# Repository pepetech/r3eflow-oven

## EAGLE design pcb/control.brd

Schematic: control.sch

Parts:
B1: PKLCS1212E2400-R1; BUZZ_PIEZO_SMD
C1, C4: 10u; 0603-MINI
C2, C3, C5, C8, C9, C10, C12, C13, C16, C17, C18, C19, C20, C22, C23, C24: 100n; 0603_WAVE
C6: 220u; PANASONIC_D
C7: 470p; 0603_WAVE
C11: CAPACITOR_ELD; PANASONIC_D
C14, C15: MLCC0603; 0603_WAVE
C25: 4u7; 0603_WAVE
C26: 10u; 0603_WAVE
C27: 1u; 0603_WAVE
D1: SK54L; DO214AA
D2, D5, D6: LED0603; CHIPLED_0603
D3: SMAJ36A; DO214AC
D4: SP0503BAHT; SOT143
D7, D8, D9, D10, D11, D12, D13, D14: SK9822; 2020
GND: PTC1812
J1, J3: PCC-SMP
J2: 2X1_2.54
J4: MICROSD; MICRO-SD
J5, J8, J9: 2EDG-2P
J6: 3X1_2.54
J7: 4P-PC-FAN; KF2510-3+1P
J10: USB-C
L1: 6.8uH; _1207
M1: HM-11
Q1, Q2, Q3, Q4: BC817-40; SOT-23-3
R1: 10M; 0603_WAVE
R2: 10k; 0603_WAVE
R3, R11: RESISTOR0603; 0603_WAVE
R4, R23: 100; 0603_WAVE
R5, R20, R21, R22, R28, R35: 100k; 0603_WAVE
R6: 3k01; 0603_WAVE
R7: 953; 0603_WAVE
R8: 300k; 0603_WAVE
R9: 47k; 0603_WAVE
R10, R24, R26, R29, R32: 220; 0603_WAVE
R12, R13, R14, R15: 4k7; 0603_WAVE
R16: 33k; 0603_WAVE
R17, R18, R19, R25, R27: 1k; 0603_WAVE
R30: 22.1k; 0603_WAVE
R31: 47.5k; 0603_WAVE
R33, R34: 5.1k; 0603_WAVE
SW1: PUSH_BUTTON
TC1: TC2050-IDC
U1: MIC4682; SOIC8
U2, U4: MCP9600; TQFN20-5X5
U3: SST26VF064B; WSOIC8
U5, U8, U9: 74LVC1G17; SC70-5
U6: CP2102N; QFN24
U7: ER-TFT035-6BOT; ZIF50-TFT_BACK
U10: EFM32GG11B4XX_Q100; QFP100
Y1: 8MHz; 2-SMD-5X3
Y2: 32.768KHz; CM200S

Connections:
3.3V: C2.P$1, C5.P$1, C8.P$1, C9.P$1, C10.P$1, C12.P$1, C13.P$1, C14.P$1, C15.P$1, C16.P$1, C17.P$1, C18.P$1, C19.P$1, C20.P$1, C22.P$1, C24.P$1, C25.P$1, J4.4, M1.9 (VCC), R3.P$2, R5.P$2, R11.P$2, R12.P$2, R13.P$2, R14.P$2, R15.P$2, R24.P$1, R26.P$1, R28.P$2, R35.P$2, TC1.1, U2.8 (VDD), U3.8 (VCC), U4.8 (VDD), U4.16 (ADDR), U6.5 (VIO), U6.6 (VDD), U6.7 (VREGIN), U7.7 (IM0), U7.8 (IM1), U7.9 (IM2), U7.35 (!RD), U7.40 (VDDI), U7.41 (VDDI), U7.42 (VCI), U10.8 (IOVDD0), U10.17 (IOVDD0), U10.31 (IOVDD0), U10.41 (AVDD), U10.44 (IOVDD0), U10.45 (AVDD), U10.57 (DVDD), U10.73 (VREGO), U10.82 (IOVDD0)
5V: C4.1, C6.+ (AN), C23.P$1, C26.P$1, D7.5 (VDD), D8.5 (VDD), D9.5 (VDD), D10.5 (VDD), D11.5 (VDD), D12.5 (VDD), D13.5 (VDD), D14.5 (VDD), J6.P$2, L1.2, R6.P$2, R21.P$2, R23.P$2, U5.5 (VCC), U7.1 (LEDA), U8.5 (VCC), U9.5 (VCC), U10.72 (VREGI), U10.79 (VBUS)
5V-SENSE: U10.50 (PD4)
12V: C1.1, C11.+ (AN), D3.C, GND.P$1 (1), J7.2, R1.P$2, R8.P$2, R22.P$2, U1.5 (IN)
!5V-ERR: U10.48 (PD2)
!RESET: SW1.1, SW1.2, TC1.10, U10.36 (!RESET)
!TFT_RESET: U7.10 (!RESET), U10.14 (PB5)
!TTFT-IRQ: U7.46 (X-/!IRQ!), U10.12 (PB3)
!TTFT-RST: U7.47 (Y-/!RST!), U10.15 (PB6)
BLE-!RST: M1.11 (!RST!), U10.60 (PE0)
BLE-KEY: M1.16 (PIO0), U10.61 (PE1)
DECOUPLE: C27.P$1, U10.59 (DECOUPLE)
DOOR-SW: C3.P$1, R4.P$2, U10.56 (PC7)
GND: C1.2, C2.P$2, C3.P$2, C4.2, C5.P$2, C6.- (CA), C7.P$2, C8.P$2, C9.P$2, C10.P$2, C11.- (CA), C12.P$2, C13.P$2, C14.P$2, C15.P$2, C16.P$2, C17.P$2, C18.P$2, C19.P$2, C20.P$2, C22.P$2, C23.P$2, C24.P$2, C25.P$2, C26.P$2, C27.P$2, D1.A, D2.C (CA), D3.A, D4.1, D7.2 (GND), D8.2 (GND), D9.2 (GND), D10.2 (GND), D11.2 (GND), D12.2 (GND), D13.2 (GND), D14.2 (GND), J1.3-BAR, J1.4-BAR, J2.2, J3.3-BAR, J3.4-BAR, J4.6, J4.BODY1 (BODY), J4.BODY2 (BODY), J4.BODY3 (BODY), J4.BODY4 (BODY), J5.P$2, J6.P$3, J8.P$1, J9.P$2, J10.A1_B12 (GND), J10.B1_A12 (GND), J10.SHIELD0 (GND), J10.SHIELD1 (GND), J10.SHIELD2 (GND), J10.SHIELD3 (GND), M1.12 (GND), Q1.P$2 (EM2), Q2.P$2 (EM2), Q3.P$2 (EM2), Q4.P$2 (EM2), R2.P$1, R7.P$1, R9.P$1, R16.P$1, R25.P$1, R31.P$1, R33.P$1, R34.P$1, SW1.3, SW1.4, TC1.3, TC1.9, U1.2 (GND), U1.4 (SHDN), U1.6 (GND), U1.7 (GND), U2.1 (GND), U2.3 (GND), U2.5 (GND), U2.6 (GND), U2.7 (GND), U2.9 (GND), U2.10 (GND), U2.13 (GND), U2.16 (ADDR), U2.17 (GND), U2.18 (GND), U2.EXP (EP), U3.4 (GND), U4.1 (GND), U4.3 (GND), U4.5 (GND), U4.6 (GND), U4.7 (GND), U4.9 (GND), U4.10 (GND), U4.13 (GND), U4.17 (GND), U4.18 (GND), U4.EXP (EP), U5.3 (GND), U6.2 (GND), U6.PAD (GND), U7.11 (VSYNC), U7.12 (HSYNC), U7.13 (DOTCLK), U7.14 (DE), U7.15 (DB17), U7.16 (DB16), U7.17 (DB15), U7.18 (DB14), U7.19 (DB13), U7.20 (DB12), U7.21 (DB11), U7.22 (DB10), U7.23 (DB9), U7.24 (DB8), U7.25 (DB7), U7.26 (DB6), U7.27 (DB5), U7.28 (DB4), U7.29 (DB3), U7.30 (DB2), U7.31 (DB1), U7.32 (DB0), U7.39 (TE), U7.43 (GND), U7.48 (GND), U7.49 (GND), U7.50 (GND), U8.3 (GND), U9.3 (GND), U10.16 (VSS), U10.32 (VSS), U10.58 (VSS), U10.83 (VSS)
I2C0-SCL-SENS: R13.P$1, U2.19 (SCL), U4.19 (SCL), U10.53 (PD7)
I2C0-SDA-SENS: R12.P$1, U2.20 (SDA), U4.20 (SDA), U10.52 (PD6)
I2C1-SCL-TTFT: R15.P$1, U7.44 (X+/SCL), U10.40 (PB12)
I2C1-SDA-TTFT: R14.P$1, U7.45 (Y+/SDA), U10.39 (PB11)
MAIN_HFXTAL_N: U10.42 (PB13), Y1.1
MAIN_HFXTAL_P: U10.43 (PB14), Y1.2
MAIN_LFXTAL_N: U10.25 (PB8), Y2.4 (2)
MAIN_LFXTAL_P: U10.24 (PB7), Y2.1
unnamed: J2.1, R4.P$1, R5.P$1
unnamed: J6.P$1, U5.4 (Y)
unnamed: J10.B5 (CC2), R34.P$2
unnamed: B1.1 (A), R23.P$1
unnamed: J10.A5 (CC1), R33.P$2
unnamed: D7.1 (SDO), D8.3 (SDI)
unnamed: D7.4 (CLKI), U9.4 (Y)
unnamed: D7.3 (SDI), U8.4 (Y)
unnamed: D7.6 (CLKO), D8.4 (CLKI)
unnamed: D8.1 (SDO), D9.3 (SDI)
unnamed: D8.6 (CLKO), D9.4 (CLKI)
unnamed: D9.1 (SDO), D10.3 (SDI)
unnamed: D5.C (CA), U6.13 (GPIO1-RXT)
unnamed: D9.6 (CLKO), D10.4 (CLKI)
unnamed: D6.C (CA), U6.14 (GPIO0-TXT)
unnamed: D6.A (AN), R26.P$2
unnamed: B1.2 (B), Q1.P$3 (C03), R21.P$1
unnamed: Q1.P$1 (BA1), R17.P$2
unnamed: D5.A (AN), R24.P$2
unnamed: D10.1 (SDO), D11.3 (SDI)
unnamed: D10.6 (CLKO), D11.4 (CLKI)
unnamed: D11.1 (SDO), D12.3 (SDI)
unnamed: D11.6 (CLKO), D12.4 (CLKI)
unnamed: D12.1 (SDO), D13.3 (SDI)
unnamed: Q4.P$1 (BA1), R27.P$2
unnamed: D12.6 (CLKO), D13.4 (CLKI)
unnamed: D13.1 (SDO), D14.3 (SDI)
unnamed: D13.6 (CLKO), D14.4 (CLKI)
unnamed: GND.P$2 (2), J5.P$1
unnamed: D1.C, L1.1, U1.8 (SW)
unnamed: R6.P$1, R7.P$2, U1.1 (FB)
unnamed: R1.P$1, R2.P$2, U1.3 (ISET)
unnamed: D2.A (AN), R10.P$2
unnamed: M1.15 (PIO1), R10.P$1
unnamed: Q3.P$1 (BA1), R19.P$2
unnamed: J7.1, Q3.P$3 (C03)
unnamed: Q2.P$1 (BA1), R18.P$2
unnamed: J7.4, Q2.P$3 (C03), R22.P$1
unnamed: J7.3, R20.P$2
PRS-CH11-SSR-OUT: J9.P$1, U10.51 (PD5)
QSPI_CLK: U3.6 (SCK), U10.84 (PF6)
QSPI_CS0: R3.P$1, U3.1 (!CS!), U10.85 (PF7)
QSPI_D0: U3.5 (MOSI/IO0), U10.88 (PD9)
QSPI_D1: U3.2 (MISO/IO1), U10.89 (PD10)
QSPI_D2: U3.3 (!WP!/IO2), U10.90 (PD11)
QSPI_D3: U3.7 (!HOLD!/IO3), U10.91 (PD12)
SDIO-CD: J4.9 (CD), R11.P$1, U10.86 (PF8)
SDIO-CLK: J4.5, U10.97 (PE13)
SDIO-CMD: J4.3, U10.96 (PE12)
SDIO-DAT0: J4.7, U10.95 (PE11)
SDIO-DAT1: J4.8, U10.94 (PE10)
SDIO-DAT2: J4.1, U10.93 (PE9)
SDIO-DAT3: J4.2, U10.92 (PE8)
SWCLK: TC1.4, U10.76 (PF0)
SWDIO: TC1.2, U10.77 (PF1)
SWO: TC1.6, U10.78 (PF2)
TC_VIN0+: J1.1-T+, U2.2 (VIN+)
TC_VIN0-: J1.2-T-, U2.4 (VIN-)
TC_VIN1+: J3.1-T+, U4.2 (VIN+)
TC_VIN1-: J3.2-T-, U4.4 (VIN-)
TFT-DC: U7.37 (D/!C!), U10.19 (PC1)
TFT-LEDK: Q4.P$3 (C03), R29.P$1, R32.P$1
TFT-LEDK1: R29.P$2, U7.2 (LEDK)
TFT-LEDK2: R32.P$2, U7.3 (LEDK)
TIM0-CC0-BUZZ: U10.27 (PA8)
TIM0-CC2-BUZZ: R17.P$1
TIM1-CC0-TFT-BL: R25.P$2, R27.P$1, U10.9 (PB0)
TIM2-CC2FAN0-SNSE: R16.P$2, R20.P$1, U10.70 (PC10)
TIM5-CC0-FAN0-GND: R19.P$1, U10.68 (PC8)
TIM5-CC1-FAN0-CTRL: R18.P$1, U10.69 (PC9)
U0RX-USB-TX: U6.21 (TXD), U10.5 (PA4)
U0TX-USB-RX: U6.20 (RXD), U10.4 (PA3)
U1RX-BLE-TX: M1.2 (TX), U10.63 (PE3)
U1TX-BLE-RX: M1.4 (RX), U10.62 (PE2)
UART_VBUS: R30.P$1, R31.P$2, U6.8 (VBUS)
US0-LED-MOSI: U8.2 (A), U10.67 (PE7)
US0-LED-SCK: U9.2 (A), U10.65 (PE5)
US2-CLK-TFT: U7.36 (!WR!/SCL), U10.22 (PC4)
US2-CS-TFT: R35.P$1, U7.38 (!CS), U10.23 (PC5)
US2-MISO-TFT: U7.33 (SDO), U10.21 (PC3)
US2-MOSI-TFT: U7.34 (SDA), U10.20 (PC2)
USB-RST: U6.9 (RSTB), U10.3 (PA2)
USB-SUS: U6.17 (SUSPEND), U10.2 (PA1)
USB-UART-D+: D4.3, J10.A6 (DP), J10.B6 (DP), U6.3 (D+)
USB-UART-D-: D4.2, J10.A7 (DN), J10.B7 (DN), U6.4 (D-)
VIN-SENSE: C7.P$1, R8.P$1, R9.P$2, U10.46 (PD0)
V_USB: D4.4, J10.A4_B9 (VBUS), J10.B4_A9 (VBUS), R30.P$2
WTIM1-CC1-ZERO-CROSS: J8.P$2, R28.P$1, U10.64 (PE4)
WTIM2-CC0-SERVO0-SIG: U5.2 (A), U10.49 (PD3)

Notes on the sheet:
door opening servo

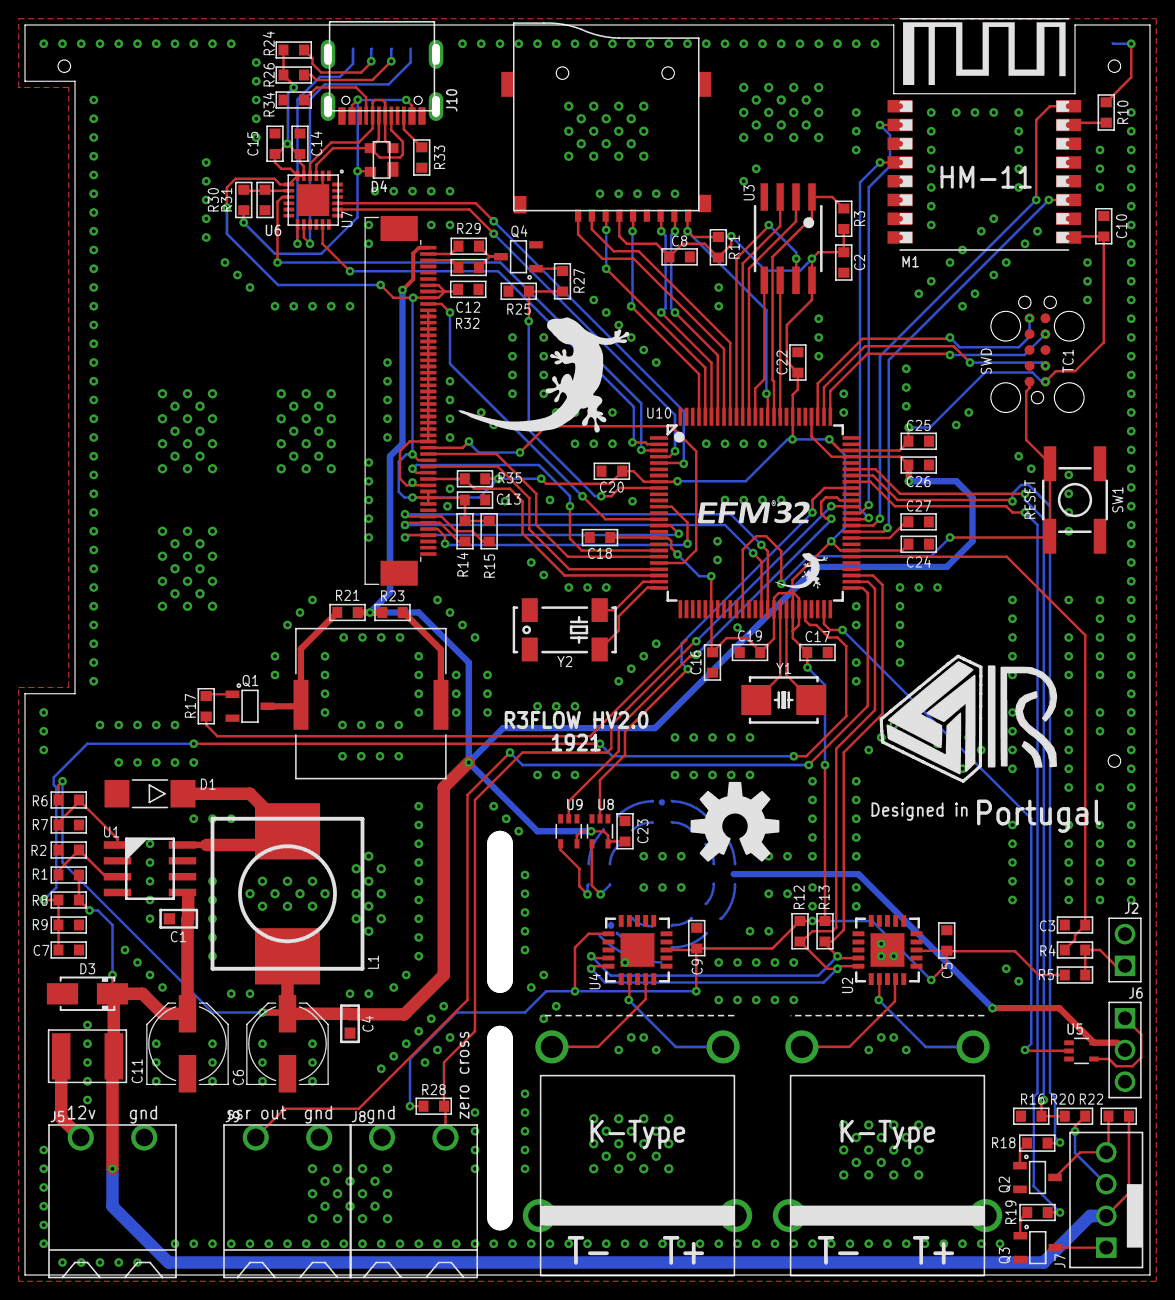
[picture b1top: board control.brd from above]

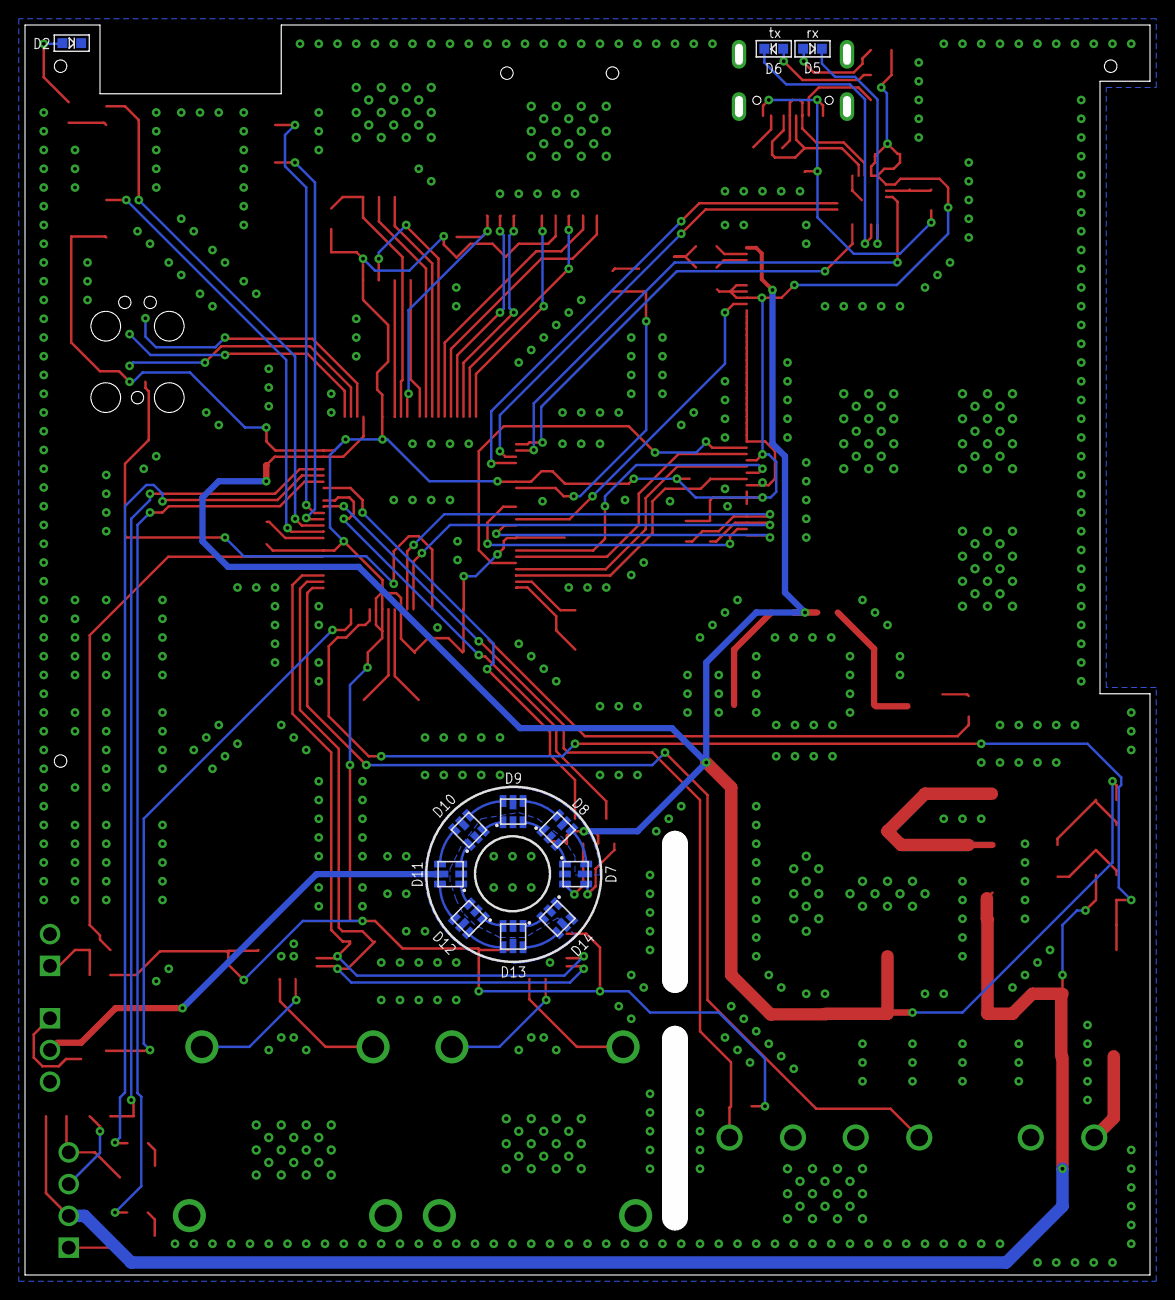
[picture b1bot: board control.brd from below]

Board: 2 copper layers, 90.0 x 100.0 mm, 111 parts (12 on the bottom side), 107 nets.

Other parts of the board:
U$1: DESIGNEDINPT
U$2: OSHW-LOGO-L
U$3: RAFAEL_SILVA_10MM_ALT
U$4: GECKO_POLY

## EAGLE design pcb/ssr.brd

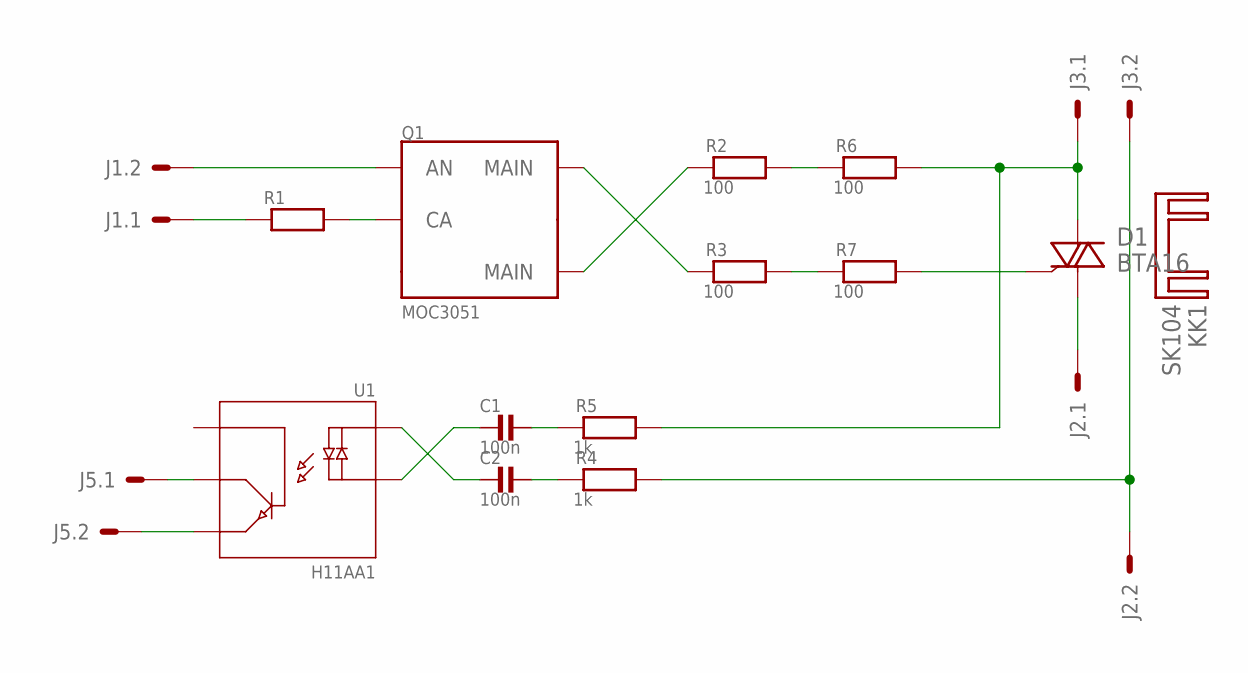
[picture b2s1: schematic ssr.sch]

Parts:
C1, C2: 100n; _1206
D1: BTA16; TO220DS
J1, J2, J3, J5: 2EDG-2P
KK1: SK104
Q1: MOC3051; DIP-6-SMD
R1: 220; 0603_WAVE
R2, R3, R6, R7: 100; _1206
R4, R5: 1k; _1206
U1: H11AA1; DIP-6-SMD

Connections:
GND: J1.P$1, R1.P$1
GND1: J5.P$2, U1.P$4 (E)
unnamed: Q1.P$2 (CA), R1.P$2
unnamed: J2.P$2, J3.P$2, R4.2
unnamed: Q1.P$6 (MAIN), R2.1
unnamed: R3.2, R7.1
unnamed: Q1.P$4 (MAIN), R3.1
unnamed: D1.A2, J3.P$1, R5.2, R6.2
unnamed: D1.A1, J2.P$1
unnamed: C1.1, R5.1
unnamed: C1.2, U1.P$2 (CA)
unnamed: C2.2, U1.P$1 (AC)
unnamed: C2.1, R4.1
unnamed: R2.2, R6.1
unnamed: D1.G, R7.2
unnamed: J5.P$1, U1.P$5 (C)
unnamed: J1.P$2, Q1.P$1 (AN)

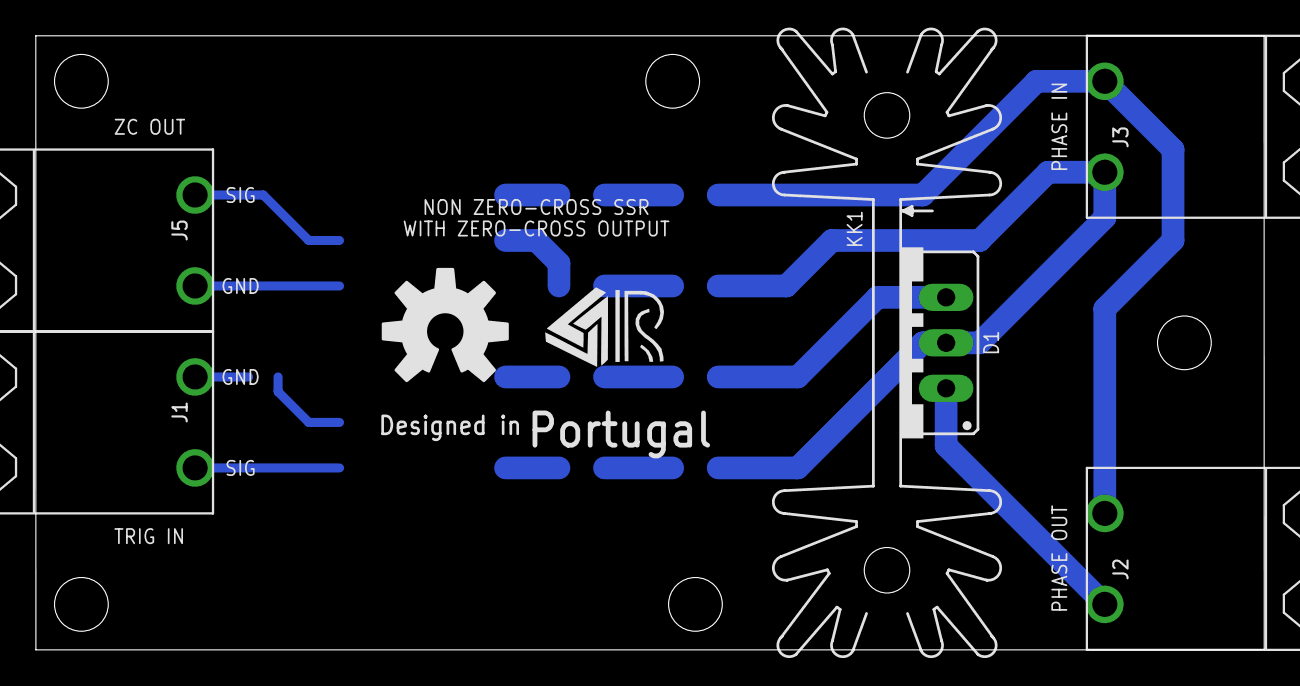
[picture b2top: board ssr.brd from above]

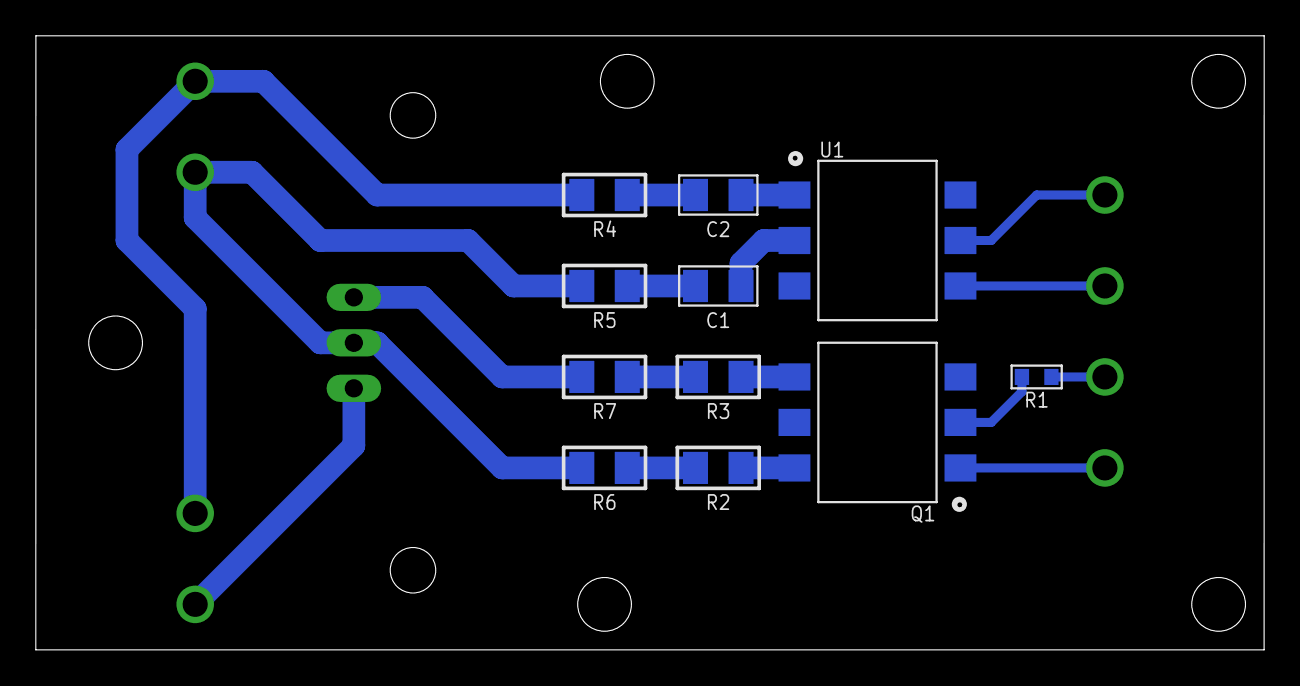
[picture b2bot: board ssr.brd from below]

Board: 2 copper layers, 68.6 x 34.3 mm, 20 parts (11 on the bottom side), 17 nets.

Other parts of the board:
U$1: DESIGNEDINPT
U$2: RAFAEL_SILVA_5MM_ALT_3
U$3: OSHW-LOGO-L

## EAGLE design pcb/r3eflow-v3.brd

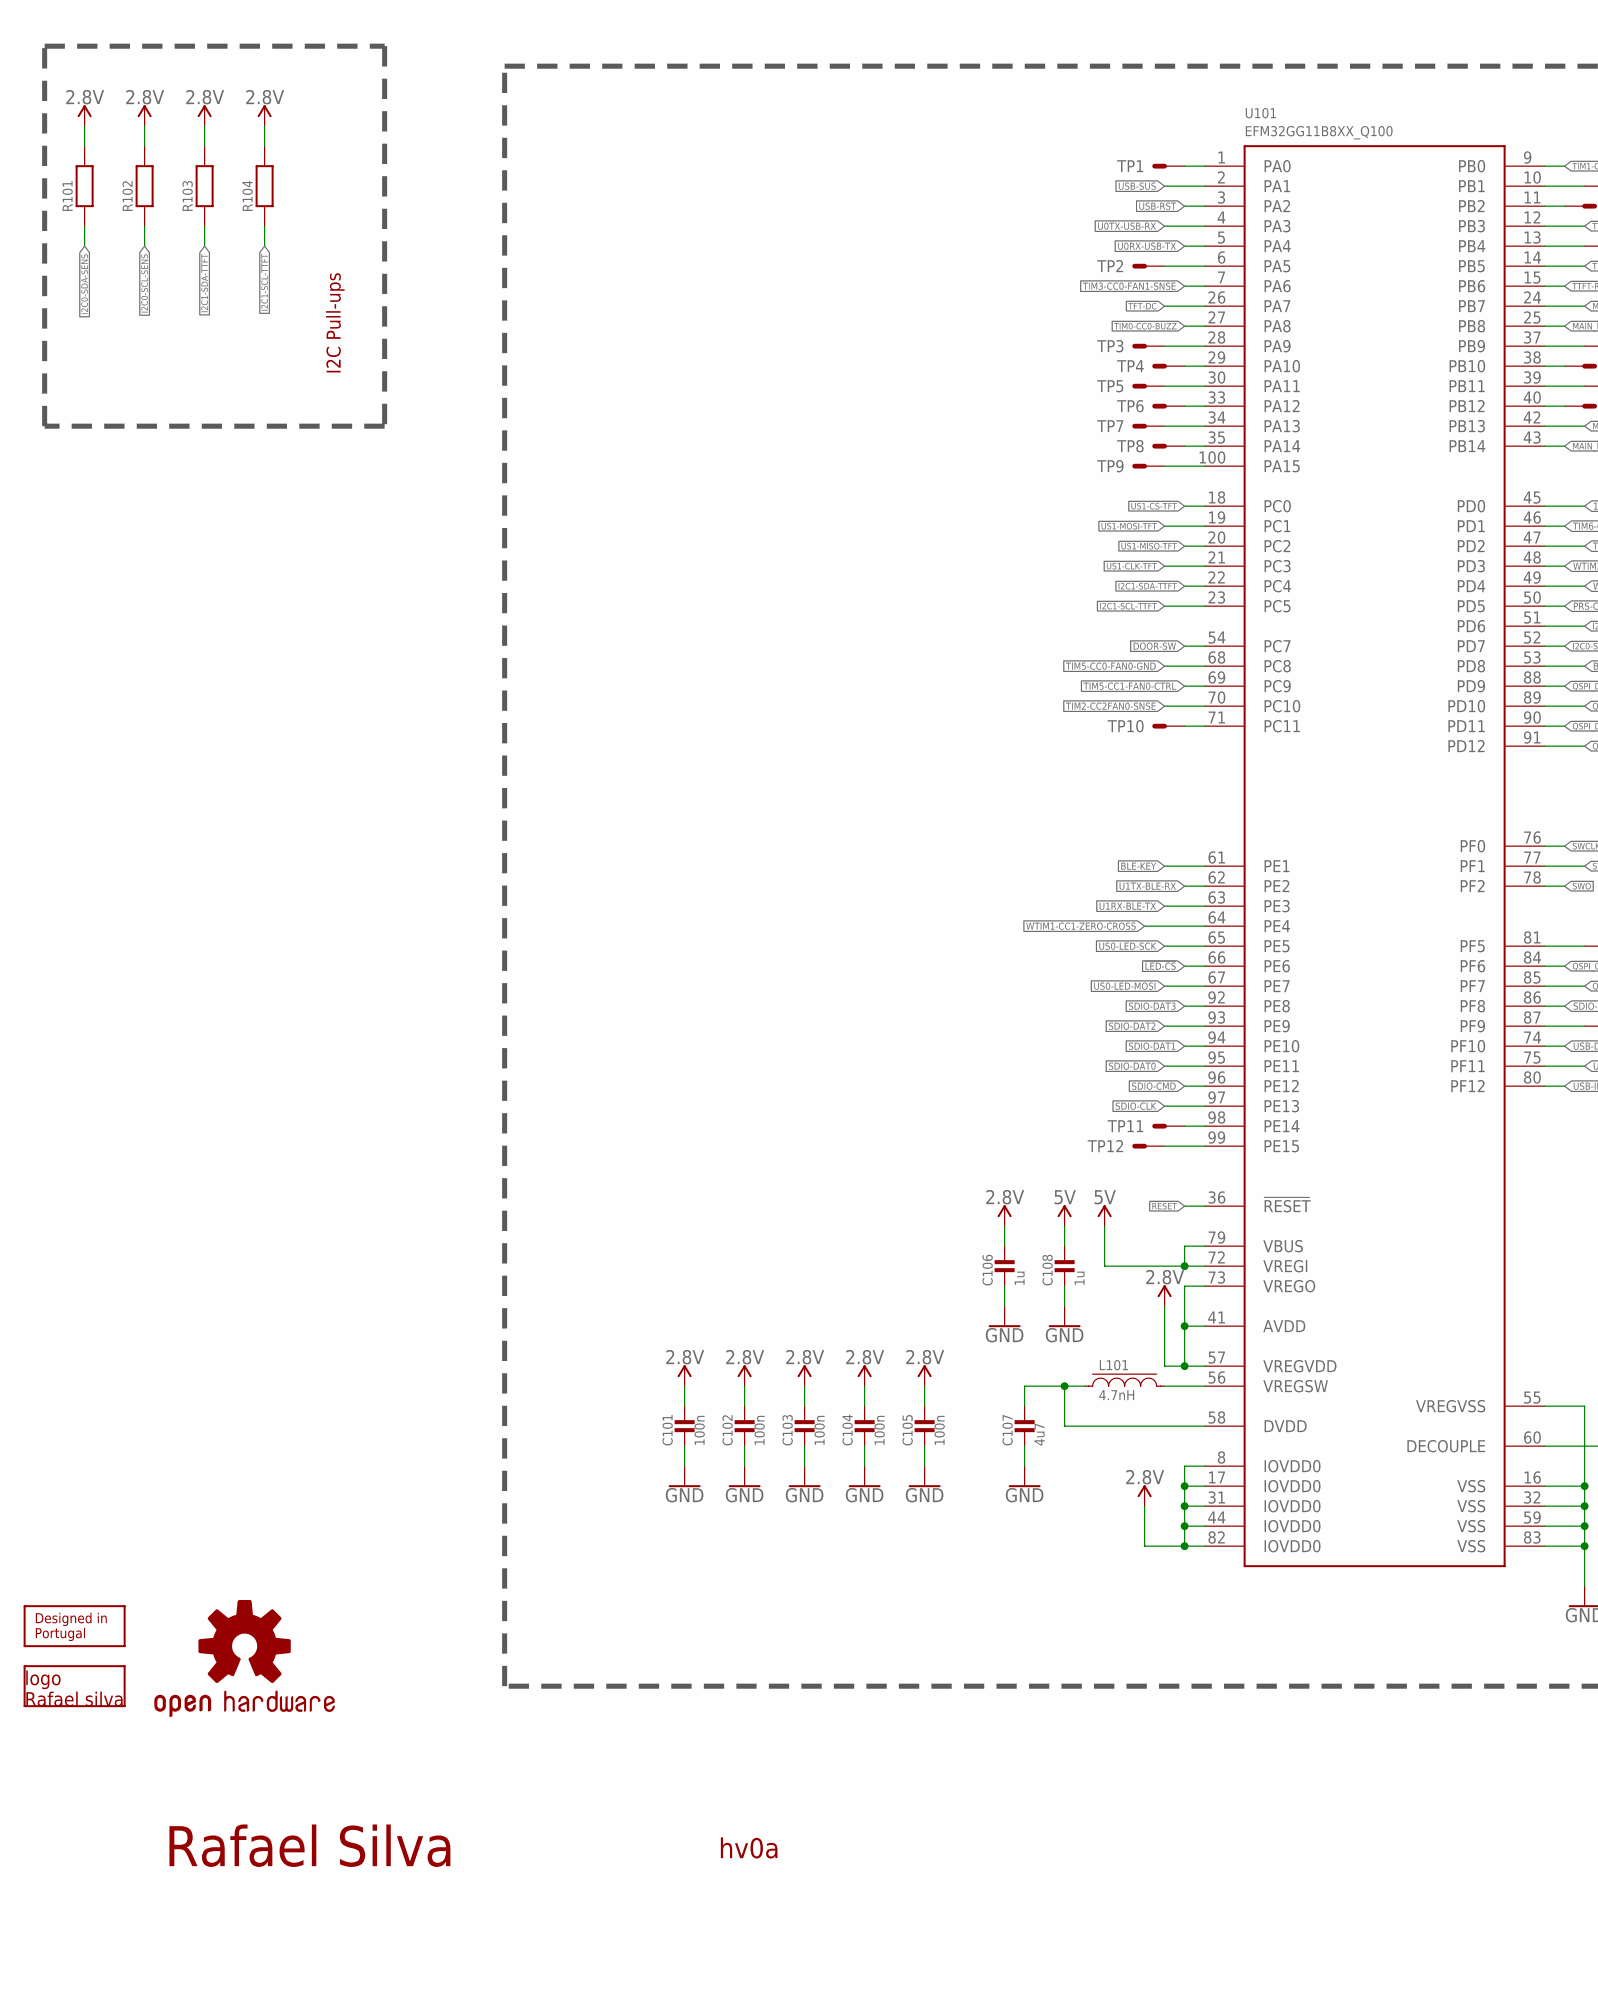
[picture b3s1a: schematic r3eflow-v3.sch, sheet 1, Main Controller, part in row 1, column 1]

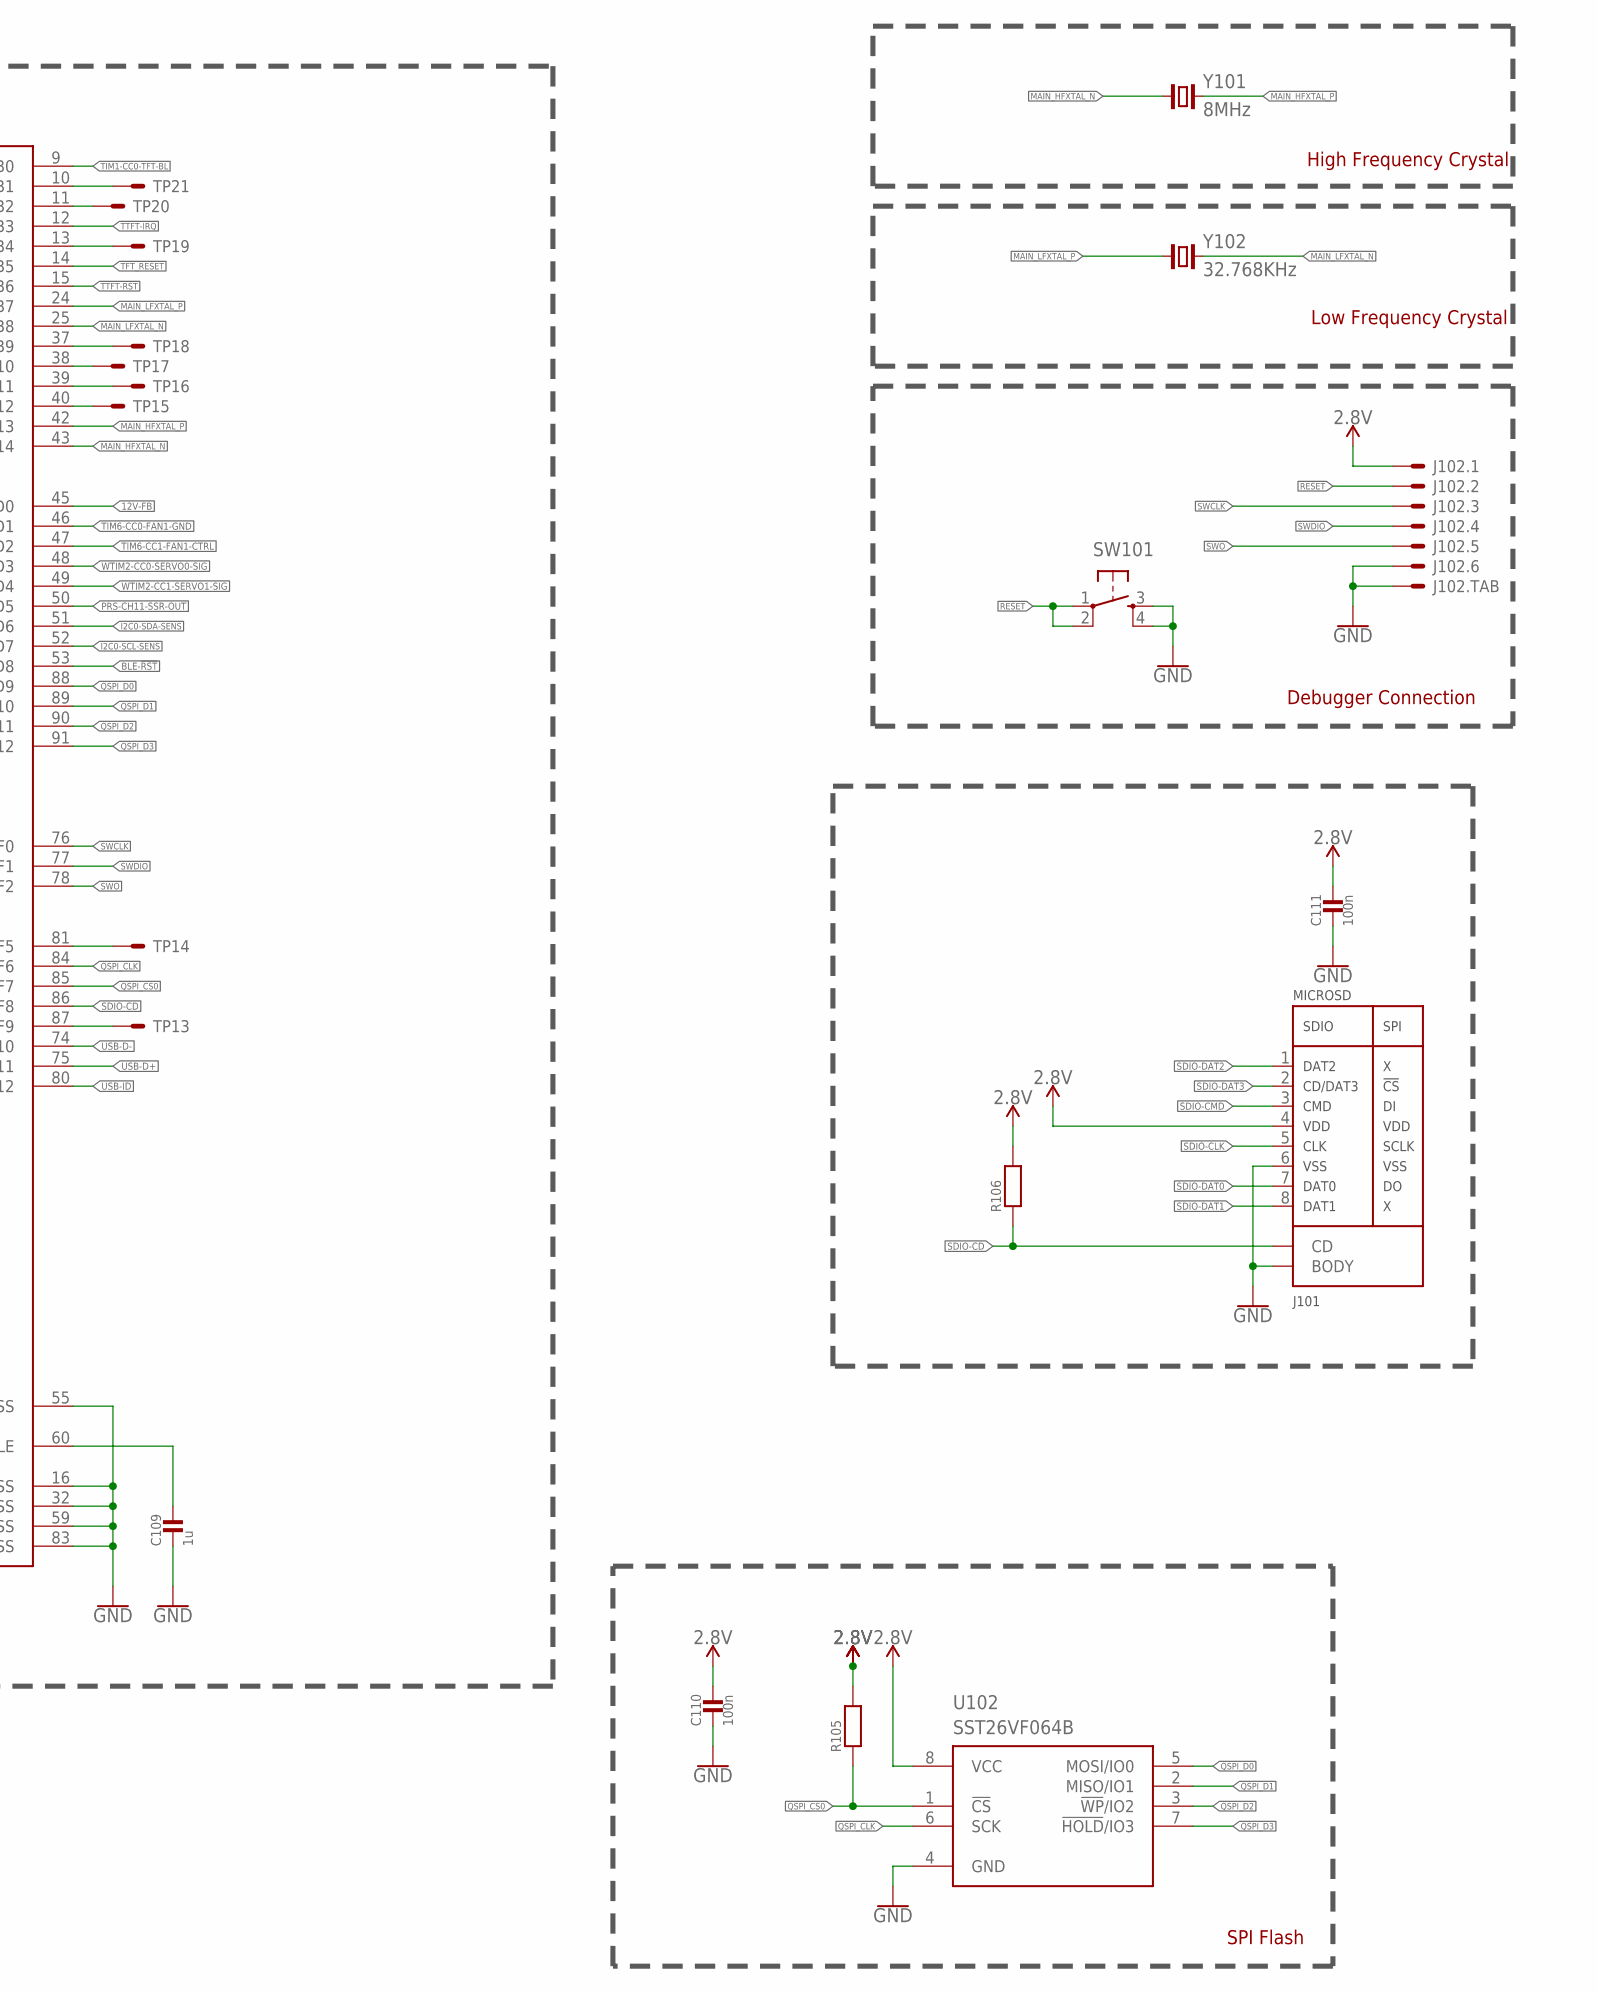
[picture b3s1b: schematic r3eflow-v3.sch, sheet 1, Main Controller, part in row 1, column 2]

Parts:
C101, C102, C103, C104, C105, C110, C111: 100n; 0603_WAVE
C106, C108, C109: 1u; 0603_WAVE
C107: 4u7; 0603_WAVE
J101: MICROSD; MICRO-SD
J102: SH-6; SM06B-SSR-H-TB
L101: 4.7nH; _0805
LOGO101: DESIGNEDINPT
LOGO102: RAFAEL_SILVA; RAFAEL_SILVA_5MM_ALT_3
LOGO103: OSHW-LOGOL; OSHW-LOGO-L
R101, R102, R103, R104, R105, R106: RESISTOR0603; 0603_WAVE
SW101: PUSH_BUTTON
TP1, TP2, TP3, TP4, TP5, TP6, TP7, TP8, TP9, TP10, TP11, TP12, TP13, TP14, TP15, TP16, TP17, TP18, TP19, TP20, TP21: TEST_POINT
U101: EFM32GG11B8XX_Q100; QFP100
U102: SST26VF064B; WSOIC8
Y101: 8MHz; 2-SMD-5X3
Y102: 32.768KHz; CM200S

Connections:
2.8V: C101.P$1, C102.P$1, C103.P$1, C104.P$1, C105.P$1, C106.P$1, C110.P$1, C111.P$1, J101.4, J102.1, R101.P$2, R102.P$2, R103.P$2, R104.P$2, R105.P$2, R106.P$2, U101.8 (IOVDD0), U101.17 (IOVDD0), U101.31 (IOVDD0), U101.41 (AVDD), U101.44 (IOVDD0), U101.57 (VREGVDD), U101.73 (VREGO), U101.82 (IOVDD0), U102.8 (VCC); also elsewhere on the board
5V: C108.P$1, U101.72 (VREGI), U101.79 (VBUS); also elsewhere on the board
12V-FB: U101.45 (PD0); also elsewhere on the board
!LED-CS: U101.66 (PE6); also elsewhere on the board
!RESET: J102.2, SW101.1, SW101.2, U101.36 (!RESET)
!TFT_RESET: U101.14 (PB5); also elsewhere on the board
!TTFT-IRQ: U101.12 (PB3); also elsewhere on the board
!TTFT-RST: U101.15 (PB6); also elsewhere on the board
BLE-!RST: U101.53 (PD8); also elsewhere on the board
BLE-KEY: U101.61 (PE1); also elsewhere on the board
DECOUPLE: C109.P$1, U101.60 (DECOUPLE)
DOOR-SW: U101.54 (PC7); also elsewhere on the board
DVDD: C107.P$1, L101.1, U101.58 (DVDD)
GND: C101.P$2, C102.P$2, C103.P$2, C104.P$2, C105.P$2, C106.P$2, C107.P$2, C108.P$2, C109.P$2, C110.P$2, C111.P$2, J101.6, J101.BODY1 (BODY), J101.BODY2 (BODY), J101.BODY3 (BODY), J101.BODY4 (BODY), J102.6, J102.FIT@1, J102.FIT@2, SW101.3, SW101.4, U101.16 (VSS), U101.32 (VSS), U101.55 (VREGVSS), U101.59 (VSS), U101.83 (VSS), U102.4 (GND); also elsewhere on the board
I2C0-SCL-SENS: R102.P$1, U101.52 (PD7); also elsewhere on the board
I2C0-SDA-SENS: R101.P$1, U101.51 (PD6); also elsewhere on the board
I2C1-SCL-TTFT: R104.P$1, U101.23 (PC5); also elsewhere on the board
I2C1-SDA-TTFT: R103.P$1, U101.22 (PC4); also elsewhere on the board
MAIN_HFXTAL_N: U101.43 (PB14), Y101.1
MAIN_HFXTAL_P: U101.42 (PB13), Y101.2
MAIN_LFXTAL_N: U101.25 (PB8), Y102.4 (2)
MAIN_LFXTAL_P: U101.24 (PB7), Y102.1
PA0: TP1.1, U101.1 (PA0)
PA5: TP2.1, U101.6 (PA5)
PA9: TP3.1, U101.28 (PA9)
PA10: TP4.1, U101.29 (PA10)
PA11: TP5.1, U101.30 (PA11)
PA12: TP6.1, U101.33 (PA12)
PA13: TP7.1, U101.34 (PA13)
PA14: TP8.1, U101.35 (PA14)
PA15: TP9.1, U101.100 (PA15)
PB1: TP21.1, U101.10 (PB1)
PB2: TP20.1, U101.11 (PB2)
PB4: TP19.1, U101.13 (PB4)
PB9: TP18.1, U101.37 (PB9)
PB10: TP17.1, U101.38 (PB10)
PB11: TP16.1, U101.39 (PB11)
PB12: TP15.1, U101.40 (PB12)
PC11: TP10.1, U101.71 (PC11)
PE14: TP11.1, U101.98 (PE14)
PE15: TP12.1, U101.99 (PE15)
PF5: TP14.1, U101.81 (PF5)
PF9: TP13.1, U101.87 (PF9)
PRS-CH11-SSR-OUT: U101.50 (PD5); also elsewhere on the board
QSPI_CLK: U101.84 (PF6), U102.6 (SCK)
QSPI_CS0: R105.P$1, U101.85 (PF7), U102.1 (!CS!)
QSPI_D0: U101.88 (PD9), U102.5 (MOSI/IO0)
QSPI_D1: U101.89 (PD10), U102.2 (MISO/IO1)
QSPI_D2: U101.90 (PD11), U102.3 (!WP!/IO2)
QSPI_D3: U101.91 (PD12), U102.7 (!HOLD!/IO3)
SDIO-CD: J101.9 (CD), R106.P$1, U101.86 (PF8)
SDIO-CLK: J101.5, U101.97 (PE13)
SDIO-CMD: J101.3, U101.96 (PE12)
SDIO-DAT0: J101.7, U101.95 (PE11)
SDIO-DAT1: J101.8, U101.94 (PE10)
SDIO-DAT2: J101.1, U101.93 (PE9)
SDIO-DAT3: J101.2, U101.92 (PE8)
SWCLK: J102.3, U101.76 (PF0)
SWDIO: J102.4, U101.77 (PF1)
SWO: J102.5, U101.78 (PF2)
TFT-DC: U101.26 (PA7); also elsewhere on the board
TIM0-CC0-BUZZ: U101.27 (PA8); also elsewhere on the board
TIM1-CC0-TFT-BL: U101.9 (PB0); also elsewhere on the board
TIM2-CC2FAN0-SNSE: U101.70 (PC10); also elsewhere on the board
TIM3-CC0-FAN1-SNSE: U101.7 (PA6); also elsewhere on the board
TIM5-CC0-FAN0-GND: U101.68 (PC8); also elsewhere on the board
TIM5-CC1-FAN0-CTRL: U101.69 (PC9); also elsewhere on the board
TIM6-CC0-FAN1-GND: U101.46 (PD1); also elsewhere on the board
TIM6-CC1-FAN1-CTRL: U101.47 (PD2); also elsewhere on the board
U0RX-USB-TX: U101.5 (PA4); also elsewhere on the board
U0TX-USB-RX: U101.4 (PA3); also elsewhere on the board
U1RX-BLE-TX: U101.63 (PE3); also elsewhere on the board
U1TX-BLE-RX: U101.62 (PE2); also elsewhere on the board
US0-LED-MOSI: U101.67 (PE7); also elsewhere on the board
US0-LED-SCK: U101.65 (PE5); also elsewhere on the board
US1-CLK-TFT: U101.21 (PC3); also elsewhere on the board
US1-CS-TFT: U101.18 (PC0); also elsewhere on the board
US1-MISO-TFT: U101.20 (PC2); also elsewhere on the board
US1-MOSI-TFT: U101.19 (PC1); also elsewhere on the board
USB-D+: U101.75 (PF11); also elsewhere on the board
USB-D-: U101.74 (PF10); also elsewhere on the board
USB-ID: U101.80 (PF12); also elsewhere on the board
USB-RST: U101.3 (PA2); also elsewhere on the board
USB-SUS: U101.2 (PA1); also elsewhere on the board
VREGSW: L101.2, U101.56 (VREGSW)
WTIM1-CC1-ZERO-CROSS: U101.64 (PE4); also elsewhere on the board
WTIM2-CC0-SERVO0-SIG: U101.48 (PD3); also elsewhere on the board
WTIM2-CC1-SERVO1-SIG: U101.49 (PD4); also elsewhere on the board

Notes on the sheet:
High Frequency Crystal
Low Frequency Crystal
I2C Pull-ups
Debugger Connection
SPI Flash

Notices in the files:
pcb/control.sch:
LICENSE: Licensed under GNU General Public License v3.0
software/src/peripheral/gpio.c:
TIM0-CC0-BUZZ - Location 6
TIM1-CC0-TFT-BL - Location 0
TIM5-CC0-FAN0-GND - Location 4
GPIO_P_MODEL_MODE3_PUSHPULL // WTIM2-CC0-SERVO0-SIG - Location 5
parts and their libraries:
Utility: Released under the Creative Commons
Utility: https://creativecommons.org/licenses/by-sa/4.0
